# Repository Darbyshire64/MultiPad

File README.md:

# MultiPad
An Multifunctional inspired macro pad. That im submiting for HackClub's <a href="highway.hackclub.com">highway</a>. The macro pad has a minimalist but functional design, With Multi layerd functionality

# Features

  - 9 Keys aranged in 3x3 Patern
  - Cherry MX Linear Switches
  - Multi Profile (3 Profiles)
  - OLED Displaying information and profile in use.

# Layout

|    OLED |        | ESP 32 |
|---------|--------|--------|
|    1    |    2   |    3   |
|    4    |    5   |    6   |
|    7    |    8   |    9   |

> [!Warning]
> The Below Features of the Firmware are NOT complete. The firmware currently only initalizes oled and functions as a numpad. this is because i find it hard to develop feautres  without having a platform to develop on.

# The Function Key

The Blue Function key is designed to allow changing of settings of the macro pad.

##  Setings

Hold down F(BLUE) key for 3 Seconds to enter customization mode. use 5 and 8 to scroll. Key 2 to modify option. Hold F Key again to exit and apply. 

Available Setings Below:

|Setting        | Options    | Desc        |
|---------------|------------|-------------|
|Toggle OLED    | On  Off    | Toggles OLED.   |
|Toggle NP      | On  Off    | Toggles NP      |
|Default Profile| 1 2 3      | Sets the Inital Profile|

## Live Switch Profile 

Hold F Key and Key 7 for 3 seconds. OLED and Neo Pixle Will light regardless of settings. and use keys 4-6 to select profile and use Key 7 to exit.

# Photos
## Case

# PCB 

# BOM

|QTY| Item                      | *Price | Link                               |
|---|---------------------------|--------|------------------------------------|
| 9 | Cherry MX Linear          | £11.61 | <a href="https://www.digikey.co.uk/en/products/detail/cherry-americas-llc/MX2A-L1NN/21738390">Link</a>|
| 1 | Seed Studio XIAO RP2040   | £3.44  |<a href="https://www.digikey.co.uk/en/products/detail/seeed-technology-co-ltd/102010428/14672129">Link</a>|
| 1 | 0.91 OLED SSD1306 Dsiplay | N/A    | N/A |
| 5 | *Custom PCB               | $2.37  | N/A |
| 2 | *3D Printed Case          | *£0    | N/A |
| 9 | THT 1N4148 Diodes         | £0.63  |<a href="https://www.digikey.co.uk/en/products/detail/onsemi/1N4148/458603">Link</a>|
| 8 | *White DSA Keycaps        | £34.96 |<a href="https://www.digikey.co.uk/en/products/detail/adafruit-industries-llc/4998/14552195">Link</a>|
| 3 | M3 Heatset Inserts        | N/A    | N/A |
| 3 | M3x16mm Screws            | N/A    | N/A |

* Price Sourced from DigiKey UK in GBP Excluding VAT
* PCB Price from JLC PCB in usd excluding shiping or any coupons from HC.
* 2 Cases because i made two case designs.
* 8 key caps because i have 1 blue one already i would like to use
* Price is free because printed via printing legion. IDK delivery cost so 0 for now but acount for delivery

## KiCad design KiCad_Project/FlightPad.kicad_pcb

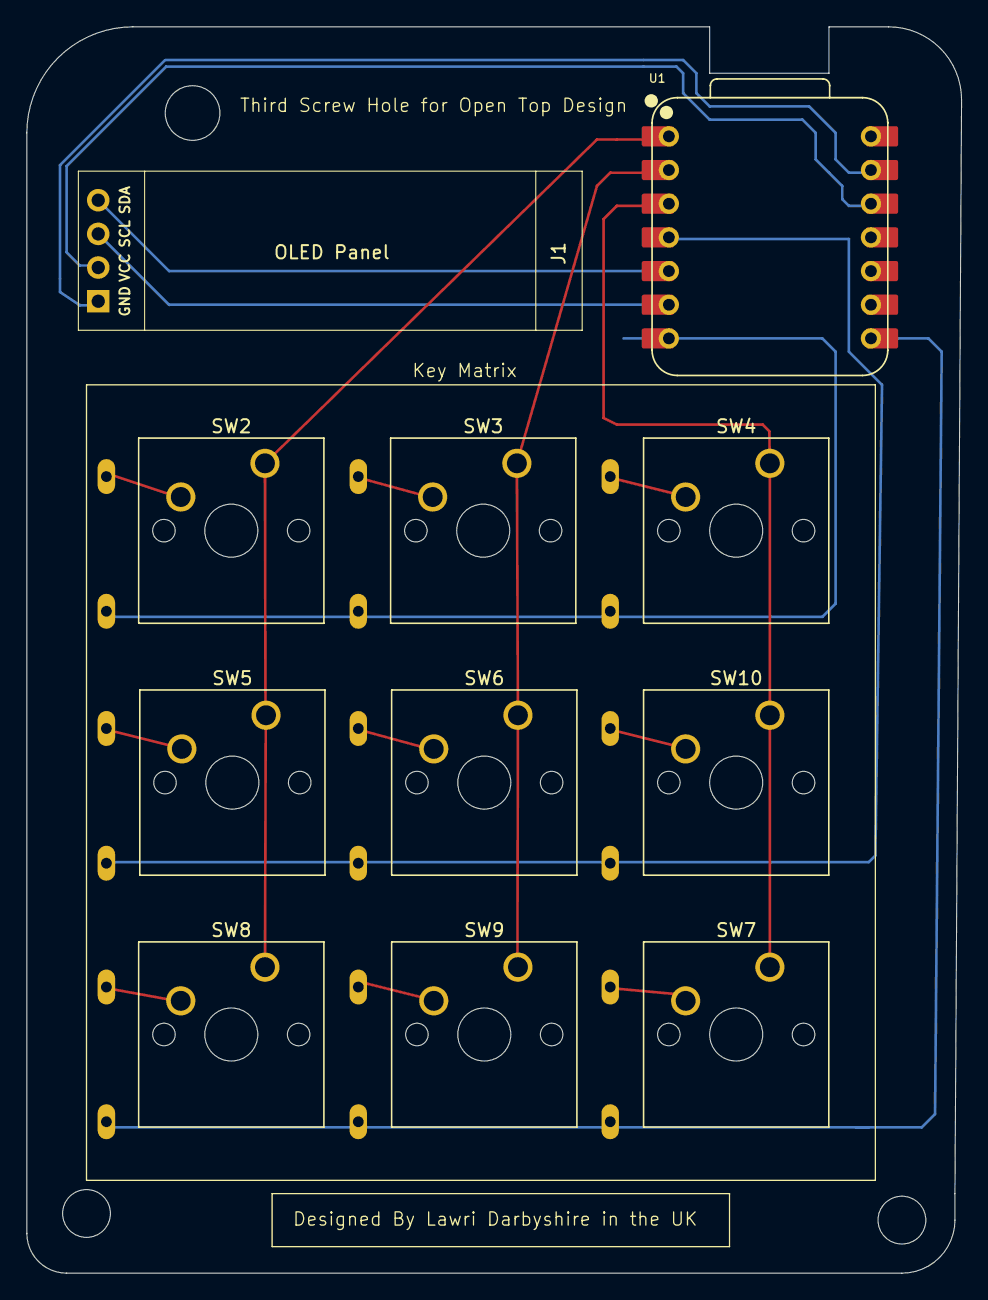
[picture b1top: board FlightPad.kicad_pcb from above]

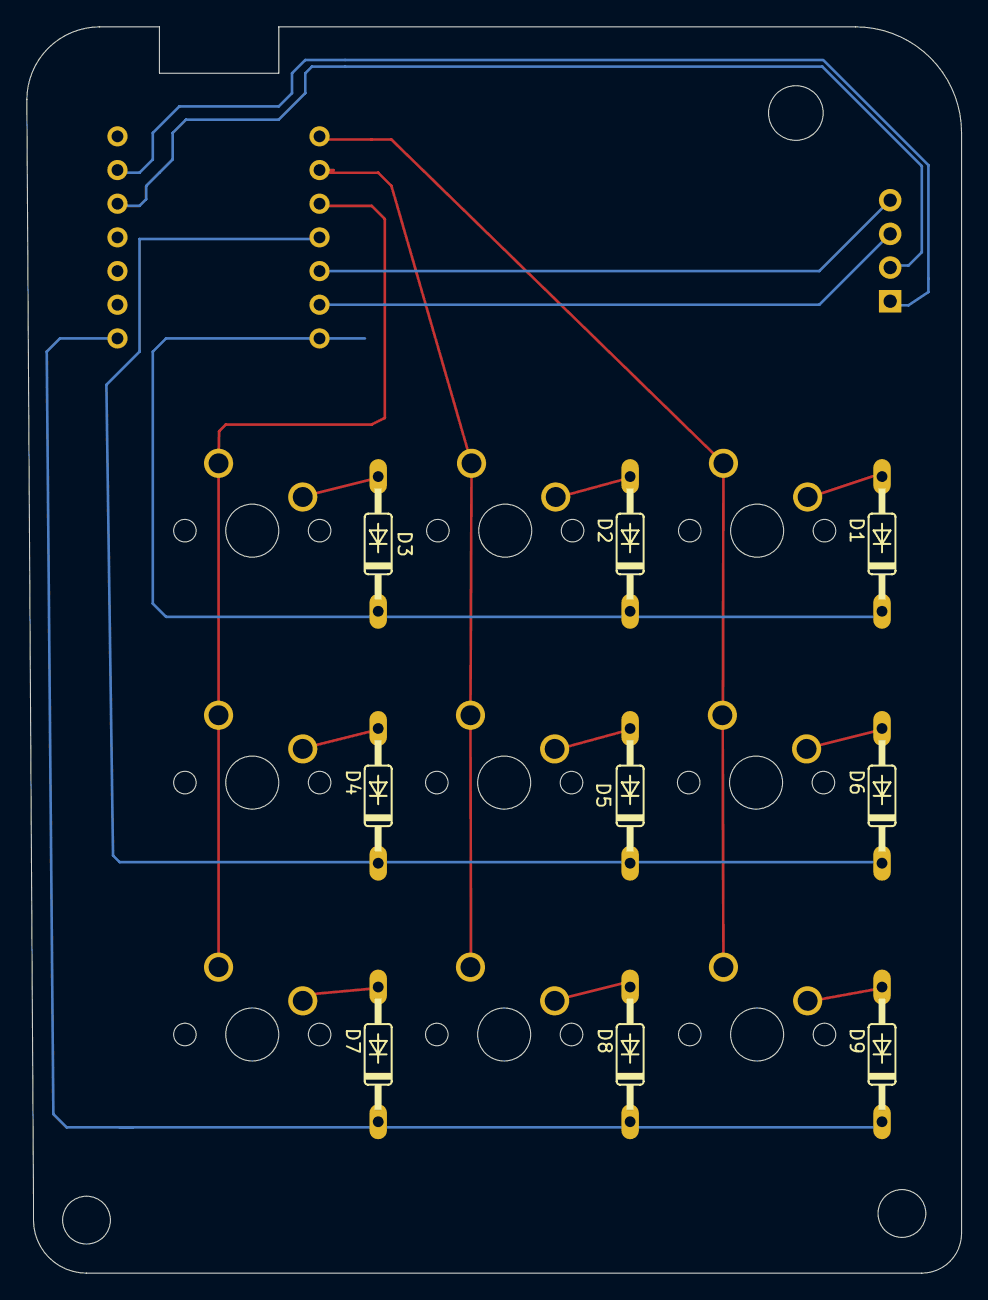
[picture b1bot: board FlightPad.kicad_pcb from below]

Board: 2 copper layers, 70.5 x 94.0 mm, 20 parts (9 on the bottom side), 7 nets.

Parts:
D1, D2, D3, D4, D5, D6, D7, D8, D9: D; DO35-10
J1: Conn_01x04_Pin; SSD1306-0.91-OLED-4pin-128x32
SW2, SW3, SW4, SW5, SW6, SW7, SW8, SW9, SW10: SW_Push; SW_Cherry_MX_1.00u_PCB
U1: XIAO-RP2040-DIP

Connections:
+3V3: J1.2, U1.12 (3V3)
COL-1: SW2.1, SW5.1, SW8.1, U1.1 (GPIO26/ADC0/A0)
COL-2: SW3.1, SW6.1, SW9.1, U1.2 (GPIO27/ADC1/A1)
COL-3: SW4.1, SW7.1, SW10.1, U1.3 (GPIO28/ADC2/A2)
GND: J1.1, U1.13 (GND)
SCL: J1.3, U1.6 (GPIO7/SCL)
SDA: J1.4, U1.5 (GPIO6/SDA)

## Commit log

2025-07-13 Added KMK Firmware.
2025-07-13 Mistake with last commit name i actualy added firmware here
2025-07-13 Worked On Firmware
2025-07-13 Prepared the files
2025-07-13 Added BOM csv format
